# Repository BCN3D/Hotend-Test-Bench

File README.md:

# Hotend test bench
This project is a test bench for BCN3D Technologies.

It consist on a electronics Board to test out 6 Hotends at a time. It basically heats up the 6 hotends to a specified temperature and then cools them down.
It verifies that the time to do the cycle is correct.

![Hotend Test Jig][system]

[system]:  https://github.com/BCN3D/Hotend-Test-Jig/blob/master/img/system.JPG

#### Folders

- _BOM: _ here you can find the electronic components for the board.
- _Code:_ the files of the firmware for the microcontroller. It has been developed in Atmel Studio 7.0
- _Gerbers:_ the gerber files of the board.
- _TemperaturesPlotter:_ Processing file that plots the temperatures sent by the board. It is exported to Windows based systems in order to run the program without installing processing IDE.
- _Eagle files:_ original design files in CadSoft Eagle.
- _img:_ just some pictures of the project.

## Electronics
The electronics consist on a board with an ATmega328, 6 Power Mosfets and 2 Leds for each power channel to display the status.
The temperature is sensed by the hotend thermistors and each signal goes to a ADC channel of the microcontroller.

The 12 LEDs are driven by 2 8-bit shift registers.

It is powered by a 24V/320W switching Power supply and a +5V LDO for the logic.
For communication, it has FTDI compatible pin headers.

Board Front

![Board Front][board_front]

Board Rear

![Board Rear][board_rear]

[board_front]: https://github.com/BCN3D/Hotend-Test-Jig/blob/master/img/board_front.JPG
[board_rear]: https://github.com/BCN3D/Hotend-Test-Jig/blob/master/img/board_rear.JPG

## Code
The code uses the [PID library](http://playground.arduino.cc/Code/PIDLibrary) for Arduino and a home made [hotend class](https://github.com/BCN3D/Hotend-Test-Jig/blob/master/Code/hotend.h).

The conversion to temperature is calculated with the Steinhart-Hart equation. You can find the guidelines of this conversion in the [adafruit learning system](https://learn.adafruit.com/thermistor?view=all). It would be better to do some table look-up but the code is harder...

First it does a startup flashing the LEDs, opens a Serial port and then it checks if the hotends are connected or not by checking the thermistor resistance.

Then the heat up process starts. Every 500ms a packet is sent through the serial port with the six temperatures. This packet is received by the computer and a [Processing](http://processing.org) program plots the data.

Main Screen of the Processing program:

![TemperaturesPlotter][plotter]

[plotter]: https://github.com/BCN3D/Hotend-Test-Jig/blob/master/img/temperaturePlotter.PNG

When the  hotends are heating, the LEDs blink as well. Finally, when the target temperature is reached, the hotends start cooling down with the help of a couple of fans.

The code computes the time it took to heat up each hotend and then decides if the time is between the established limits.
## Mechanics

The Mechanics are quite simple. Basically we designed a bench to hold the hotends in place and to prevent the operator from burning. the black pieces are 3mm aluminum painted in matt black and the white pieces are 3D printed.

The cover from behind is a 3mm PMMA sheet laser cut and handcrafted bent.

## To do in the TemperaturesPlotter
- [ ] Clear button to clear the graph area.
- [ ] Start the time when the COM port is selected.
- [ ] Fix the target temperature bar to the correct temperature.
- [ ] Calculate the time to heat for each hotend
- [ ] Export data to a `.xmml` or `.csv` file and import it in Excel. To Database purposes
- [x] Splash Screen.
- [ ] Mouse gives you temperature in the graph.

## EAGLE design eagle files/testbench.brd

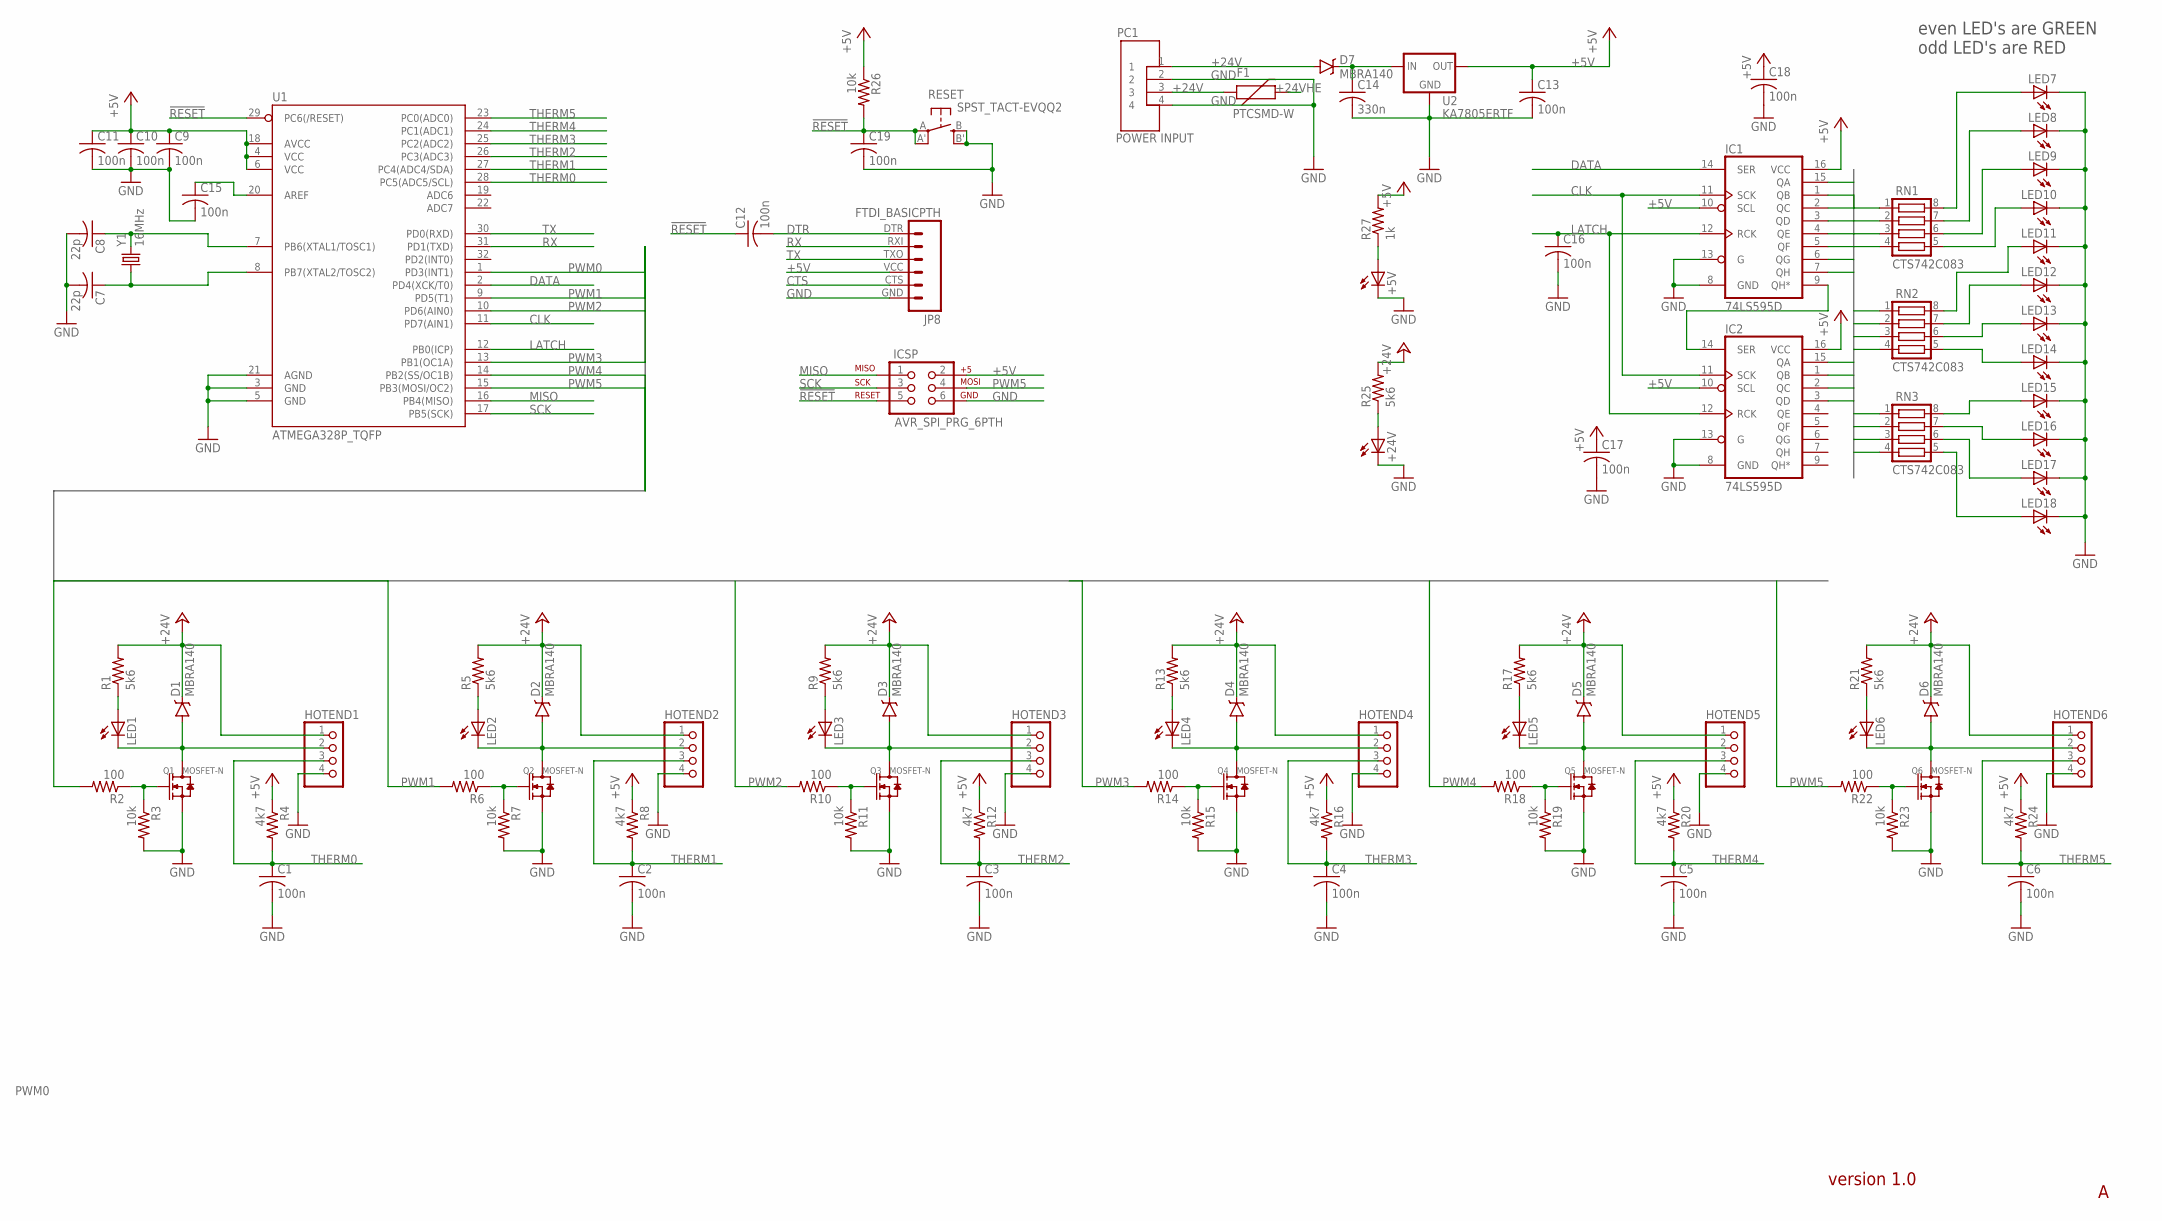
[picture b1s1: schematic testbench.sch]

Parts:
+5V, +24V: LEDCHIP-LED0805; CHIP-LED0805; MPN OVS-0803
C1, C2, C3, C4, C5, C6, C9, C10, C11, C12, C13, C15, C16, C17, C18, C19: 100n; C0805K; MPN 08051C104KAT2A
C7, C8: 22p; C0805K; MPN 08051A220JAT2A
C14: 330n; C0805K; MPN 08055C334KAT2A
D1, D2, D3, D4, D5, D6, D7: MBRA140; SMA-DIODE; MPN B140-13-F
F1: PTCSMD-W; PTC-1206-WIDE; MPN 3413.0329.22
HOTEND1, HOTEND2, HOTEND3, HOTEND4, HOTEND5, HOTEND6: PINHD-1X4; 1X04
IC1, IC2: 74LS595D; SO16; MPN SN74AHCT595D
ICSP: AVR_SPI_PRG_6PTH; 2X3
JP8: FTDI_BASICPTH; FTDI_BASIC
LED1, LED2, LED3, LED4, LED5, LED6, LED7, LED8, LED9, LED10, LED11, LED12, LED13, LED14, LED15, LED16, LED17, LED18: LEDCHIP-LED0805; CHIP-LED0805; MPN OVS-0803
PC1: POWER INPUT; MOLEX_MINIFIT-JR; MPN 39303045
Q1, Q2, Q3, Q4, Q5, Q6: MOSFET-N; SOIC8; MPN IRF8736PBF
R1, R5, R9, R13, R17, R21, R25: 5k6; R0805; MPN MCWR08X5601FTL
R2, R6, R10, R14, R18, R22: 100; R0805; MPN ERA6AEB101V
R3, R7, R11, R15, R19, R23, R26: 10k; R0805; MPN 0621-013K500-AB103
R4, R8, R12, R16, R20, R24: 4k7; R0805; MPN 1-2176085-7
R27: 1k; R0805; MPN CR0805-JW-102ELF
RESET: SPST_TACT-EVQQ2; EVQ-Q2; MPN EVQQ2503W
RN1, RN2, RN3: CTS742C083
U1: ATMEGA328P_TQFP; TQFP32-08; MPN ATMEGA328-AU
U2: KA7805ERTF; TO-252; MPN KA7805ERTF
Y1: 16MHz; HC49US; MPN 9B-20.000MAAJ-B

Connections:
!RESET: C12.1, C19.1, ICSP.5, R26.2, RESET.A, RESET.A' (P1), U1.29 (PC6(/RESET))
+5V: C9.1, C10.1, C11.1, C13.1, C17.1, C18.1, IC1.10 (SCL), IC1.16 (VCC), IC2.10 (SCL), IC2.16 (VCC), ICSP.2, JP8.VCC (4), R4.1, R8.1, R12.1, R16.1, R20.1, R24.1, R26.1, R27.2, U1.4 (VCC), U1.6 (VCC), U1.18 (AVCC), U2.2 (OUT)
+24V: D7.A, F1.1, PC1.1, PC1.3, R25.2
+24VHE: D1.C, D2.C, D3.C, D4.C, D5.C, D6.C, F1.2, HOTEND1.1, HOTEND2.1, HOTEND3.1, HOTEND4.1, HOTEND5.1, HOTEND6.1, R1.2, R5.2, R9.2, R13.2, R17.2, R21.2
CLK: IC1.11 (SCK), IC2.11 (SCK), U1.11 (PD7(AIN1))
CTS: JP8.CTS (5)
DATA: IC1.14 (SER), U1.2 (PD4(XCK/T0))
DTR: C12.2, JP8.DTR (1)
GND: +5V.C, +24V.C, C1.2, C2.2, C3.2, C4.2, C5.2, C6.2, C7.2, C8.2, C9.2, C10.2, C11.2, C13.2, C14.2, C15.2, C16.2, C17.2, C18.2, C19.2, HOTEND1.4, HOTEND2.4, HOTEND3.4, HOTEND4.4, HOTEND5.4, HOTEND6.4, IC1.8 (GND), IC1.13 (G), IC2.8 (GND), IC2.13 (G), ICSP.6, JP8.GND (6), LED7.C, LED8.C, LED9.C, LED10.C, LED11.C, LED12.C, LED13.C, LED14.C, LED15.C, LED16.C, LED17.C, LED18.C, PC1.2, PC1.4, Q1.1 (S), Q1.2 (S), Q1.3 (S), Q2.1 (S), Q2.2 (S), Q2.3 (S), Q3.1 (S), Q3.2 (S), Q3.3 (S), Q4.1 (S), Q4.2 (S), Q4.3 (S), Q5.1 (S), Q5.2 (S), Q5.3 (S), Q6.1 (S), Q6.2 (S), Q6.3 (S), R3.2, R7.2, R11.2, R15.2, R19.2, R23.2, RESET.B (S), RESET.B' (S1), U1.3 (GND), U1.5 (GND), U1.21 (AGND), U2.3 (GND)
H1: D1.A, HOTEND1.2, LED1.C, Q1.5 (D), Q1.6 (D), Q1.7 (D), Q1.8 (D)
H2: D2.A, HOTEND2.2, LED2.C, Q2.5 (D), Q2.6 (D), Q2.7 (D), Q2.8 (D)
H3: D3.A, HOTEND3.2, LED3.C, Q3.5 (D), Q3.6 (D), Q3.7 (D), Q3.8 (D)
H4: D4.A, HOTEND4.2, LED4.C, Q4.5 (D), Q4.6 (D), Q4.7 (D), Q4.8 (D)
H5: D5.A, HOTEND5.2, LED5.C, Q5.5 (D), Q5.6 (D), Q5.7 (D), Q5.8 (D)
H6: D6.A, HOTEND6.2, LED6.C, Q6.5 (D), Q6.6 (D), Q6.7 (D), Q6.8 (D)
LATCH: C16.1, IC1.12 (RCK), IC2.12 (RCK), U1.12 (PB0(ICP))
LED0: IC1.15 (QA), RN2.4
LED1: IC1.1 (QB), RN2.3
LED2: IC1.2 (QC), RN2.2
LED3: IC1.3 (QD), RN2.1
LED4: IC1.4 (QE), RN1.4
LED5: IC1.5 (QF), RN1.3
LED6: IC1.6 (QG), RN1.2
LED7: IC1.7 (QH), RN1.1
LED8: IC2.15 (QA), RN3.4
LED9: IC2.1 (QB), RN3.3
LED10: IC2.2 (QC), RN3.2
LED11: IC2.3 (QD), RN3.1
MISO: ICSP.1, U1.16 (PB4(MISO))
unnamed: Q1.4 (G), R2.1, R3.1
unnamed: +24V.A, R25.1
unnamed: LED1.A, R1.1
unnamed: Q5.4 (G), R18.1, R19.1
unnamed: C7.1, U1.8 (PB7(XTAL2/TOSC2)), Y1.1
unnamed: LED7.A, RN1.8
unnamed: Q2.4 (G), R6.1, R7.1
unnamed: LED2.A, R5.1
unnamed: Q3.4 (G), R10.1, R11.1
unnamed: LED3.A, R9.1
unnamed: Q4.4 (G), R14.1, R15.1
unnamed: LED4.A, R13.1
unnamed: LED5.A, R17.1
unnamed: Q6.4 (G), R22.1, R23.1
unnamed: LED6.A, R21.1
unnamed: C8.1, U1.7 (PB6(XTAL1/TOSC1)), Y1.2
unnamed: C15.1, U1.20 (AREF)
unnamed: C14.1, D7.C, U2.1 (IN)
unnamed: LED8.A, RN1.7
unnamed: LED9.A, RN1.6
unnamed: LED10.A, RN1.5
unnamed: LED11.A, RN2.8
unnamed: LED12.A, RN2.7
unnamed: LED13.A, RN2.6
unnamed: LED14.A, RN2.5
unnamed: LED15.A, RN3.8
unnamed: LED16.A, RN3.7
unnamed: LED17.A, RN3.6
unnamed: LED18.A, RN3.5
unnamed: IC1.9 (QH*), IC2.14 (SER)
unnamed: +5V.A, R27.1
PWM0: R2.2, U1.1 (PD3(INT1))
PWM1: R6.2, U1.9 (PD5(T1))
PWM2: R10.2, U1.10 (PD6(AIN0))
PWM3: R14.2, U1.13 (PB1(OC1A))
PWM4: R18.2, U1.14 (PB2(SS/OC1B))
PWM5: ICSP.4, R22.2, U1.15 (PB3(MOSI/OC2))
RX: JP8.RXI (2), U1.31 (PD1(TXD))
SCK: ICSP.3, U1.17 (PB5(SCK))
THERM0: C1.1, HOTEND1.3, R4.2, U1.28 (PC5(ADC5/SCL))
THERM1: C2.1, HOTEND2.3, R8.2, U1.27 (PC4(ADC4/SDA))
THERM2: C3.1, HOTEND3.3, R12.2, U1.26 (PC3(ADC3))
THERM3: C4.1, HOTEND4.3, R16.2, U1.25 (PC2(ADC2))
THERM4: C5.1, HOTEND5.3, R20.2, U1.24 (PC1(ADC1))
THERM5: C6.1, HOTEND6.3, R24.2, U1.23 (PC0(ADC0))
TX: JP8.TXO (3), U1.30 (PD0(RXD))

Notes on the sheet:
even LED's are GREEN odd LED's are RED
version 1.0

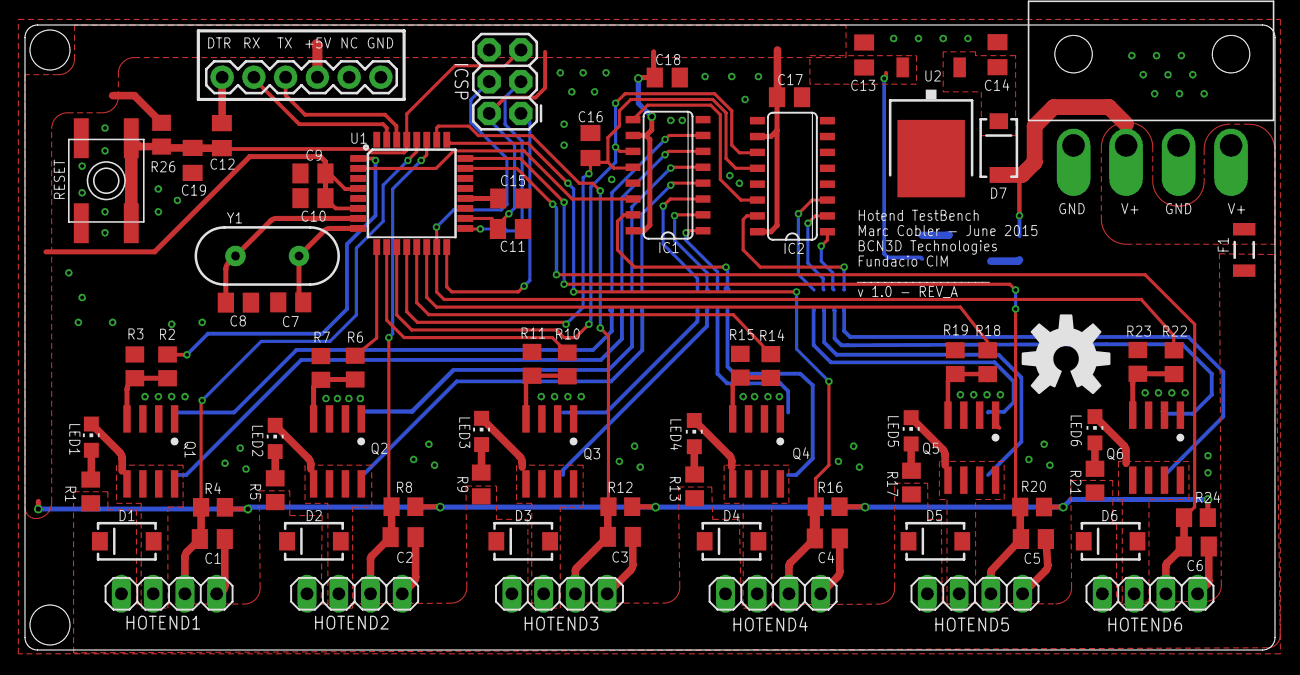
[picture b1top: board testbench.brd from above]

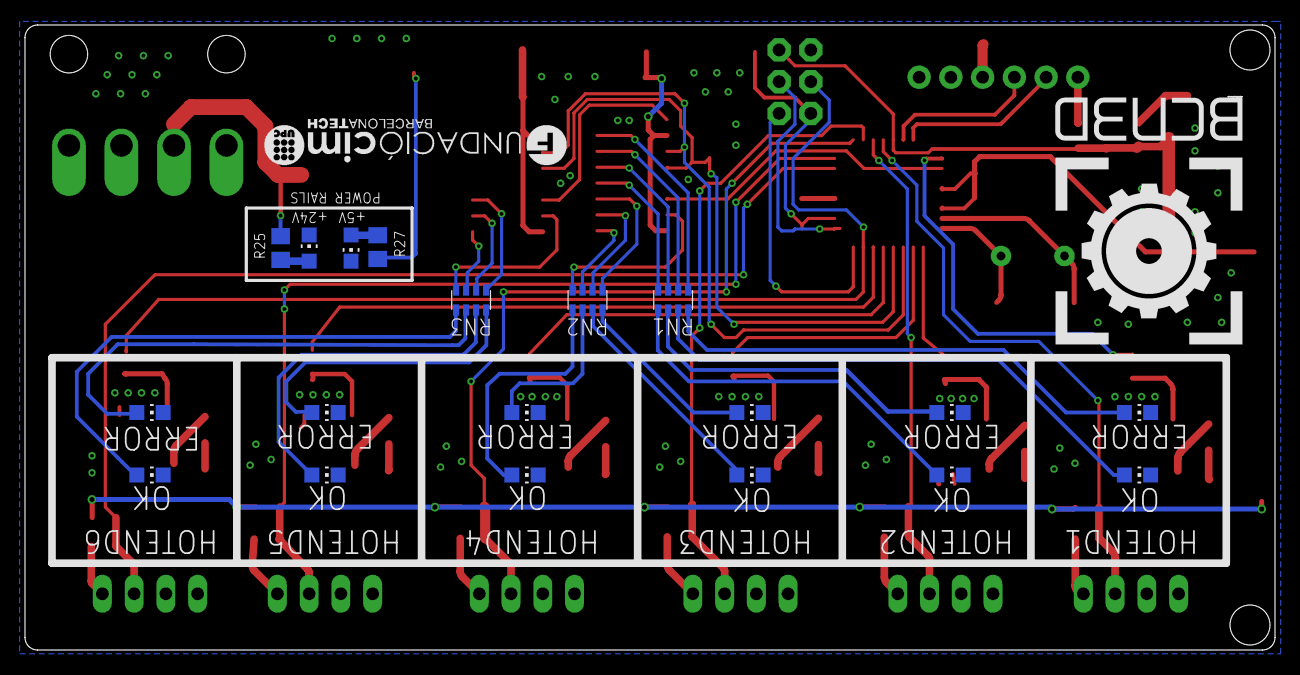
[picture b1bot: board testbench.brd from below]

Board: 2 copper layers, 100.0 x 50.0 mm, 101 parts (21 on the bottom side), 74 nets.

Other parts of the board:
U$1: FCIM_LOGO
U$2: BCN3D_LOGO
U$3: OSHW-LOGO-L

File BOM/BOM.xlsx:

Qty | Value | Device | Package | Parts | Description | MF | MPN | OC_FARNELL | OC_NEWARK | PROD_ID | VALUE
20 |  | LEDCHIP-LED0805 | CHIP-LED0805 | +5V, +24V, LED1, LED2, LED3, LED4, LED5, LED6, LED7, LED8, LED9, LED10, LED11, 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 | LED | MULTICOMP | OVS-0803 | 1716765
6 |  | PINHD-1X4 | 1X04 | HOTEND1, HOTEND2, HOTEND3, HOTEND4, HOTEND5, HOTEND6 | PIN HEADER |  |  | unknown
6 | 100 | R-US_R0805 | R0805 | R2, R6, R10, R14, R18, R22 | RESISTOR, American symbol | PANASONIC ELECTRONIC COMPONENTS | ERA6AEB101V | 1577644
16 | 100n | C-USC0805K | C0805K | C1, C2, C3, C4, C5, C6, C9, C10, C11, C12, C13, C15, C16, C17, C18, C19 | CAPACITOR, American symbol | AVX | 08051C104KAT2A | 1740681
7 | 10k | R-US_R0805 | R0805 | R3, R7, R11, R15, R19, R23, R26 | RESISTOR, American symbol | BOURNS | 0621-013K500-AB103 | 2469474
1 | 1k | R-US_R0805 | R0805 | R27 | RESISTOR, American symbol | BOURNS | CR0805-JW-102ELF | 2008389
1 | 20MHz | CRYSTALHC49US | HC49US | Y1 | Various standard crystals. Proven footprints. | TXC | 9B-20.000MAAJ-B | 1842224
2 | 22p | C-USC0805K | C0805K | C7, C8 | CAPACITOR, American symbol | AVX | 08051A220JAT2A | 317500
1 | 330n | C-USC0805K | C0805K | C14 | CAPACITOR, American symbol | AVX | 08055C334KAT2A | 1657934
6 | 4k7 | R-US_R0805 | R0805 | R4, R8, R12, R16, R20, R24 | RESISTOR, American symbol | TE CONNECTIVITY | 1-2176085-7 | 2118118
7 | 5k6 | R-US_R0805 | R0805 | R1, R5, R9, R13, R17, R21, R25 | RESISTOR, American symbol | MULTICOMP | MCWR08X5601FTL | 2447693
2 | 74LS595D | 74LS595D | SO16 | IC1, IC2 | 8-bit SHIFT REGISTER, output latch | TEXAS INSTRUMENTS | SN74HC165DR | 2436975 |  | IC-07875
1 | ATMEGA328P_TQFP | ATMEGA328P_TQFP | TQFP32-08 | U1 |  | ATMEL | ATMEGA328-AU | 1972086 |  | IC-09069 | ATMEGA328P_TQFP
1 | AVR_SPI_PRG_6PTH | AVR_SPI_PRG_6PTH | 2X3 | ICSP | AVR ISP 6 Pin |  |  | unknown
3 | CTS742C083 | CTS742C083 | CTS742C083 | RN1, RN2, RN3 | Chip Resistor Array 4 Single Resistor |  |  | unknown | unknown
1 | FTDI_BASICPTH | FTDI_BASICPTH | FTDI_BASIC | JP8 | FTDI Basic header with labels |  |  | unknown
1 | KA7805ERTF | V_REG_78XX7812 | TO-252 | U2 | Voltage Regulator | FAIRCHILD SEMICONDUCTOR | KA7805ERTF | 2102585 |  | VREG-12370 | +12v
7 | MBRA140 | MBRA140 | SMA-DIODE | D1, D2, D3, D4, D5, D6, D7 | 40V, 1A Schottky rectifier | DIODES INC. | B140-13-F | 1843670 |  | DIO-08053
6 | MOSFET-N | MOSFET-N | SOIC8 | Q1, Q2, Q3, Q4, Q5, Q6 | CJ2302:SMD MOSFET N-CH 20V-2.1A | INTERNATIONAL RECTIFIER | IRF8736PBF | 1551903
1 | POWER INPUT | POWER_CONNECTOR_4WAY | MOLEX_MINIFIT-JR | PC1 | MOLEX Mini-Fit Jr. 13A/600V Power connector REF: 39303045 | MOLEX | 39303045 | 9963553
1 | PTCSMD-W | PTCSMD-W | PTC-1206-WIDE | F1 | Resettable Fuse PTC | SCHURTER | 3413.0329.22 | 1829472
1 | SPST_TACT-EVQQ2 | SPST_TACT-EVQQ2 | EVQ-Q2 | RESET | SMT 6mm switch, EVQQ2 series | PANASONIC ELECTRONIC COMPONENTS | EVQQ2503W | 9962913

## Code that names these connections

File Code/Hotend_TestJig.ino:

/*---------------------------------------------------------------------
Hotend_TestJig.ino - main program file
HotEnd test Jig
Marc Cobler Cosmen - June 2015
BCN3D Technologies - Fundacio CIM

This program is for testing the assembled hotends in BCN3D Technologies.
It's Atmega328 based and it contains 6 power Mosfet Channels to heat up
6 hotends at a time. If the heating curve is within limits, then a Green 
LED lights up, if not a red LED lights up.


ADJUSTING PWM FREQUENCIES 
In the Arduino world timer0 is been used for the timer functions, like delay(), millis() and micros(). 
If you change timer0 registers, this may influence the Arduino timer function. 
So you should know what you are doing. 
// Note that the base frequency for pins 3, 9, 10, and 11 is 31250 Hz
// Note that the base frequency for pins 5 and 6 is 62500 Hz
-----------------------------------------------------------------------*/
#include "hotend.h"
#include "PID_v1.h"
//--------------------CONSTANTS-----------------------------------------
#define MAXTEMPERATURE 260

const char* tempSensors[]= {"THERM0","THERM1","THERM2","THERM3","THERM4","THERM5"};
#define THERM0 5
#define THERM1 4
#define THERM2 3
#define THERM3 2
#define THERM4 1
#define THERM5 0

#define HOTEND0 3 //PD3 TIMER2
#define HOTEND1 5 //PD5 TIMER0
#define HOTEND2 6 //PD6 TIMER0
#define HOTEND3 9 //PB1 TIMER1
#define HOTEND4 10 //PB2 TIMER1
#define HOTEND5 11 //PB3 TIMER2

#define CLOCK 7
#define LATCH 8
#define DATA 4

//--------------------VARIABLES-----------------------------------------
bool connectedHotends[6]= {0,0,0,0,0,0}; //Array of boolean. Indicates hotends connected
String command;
//PID Variables
double output;
double setTemperature;
//PID Settings
double kp = 1;
double kd = 0.25;
double ki = 0.05;
//bytes for the shift Registers
byte leds1 = 0;
byte leds2 = 0;


//--------------------OBJECTS-------------------------------------------
//---Let's declare de hotends objects
hotend h1(THERM0, HOTEND0);
hotend h2(THERM1, HOTEND1);
hotend h3(THERM2, HOTEND2);
hotend h4(THERM3, HOTEND3);
hotend h5(THERM4, HOTEND4);
hotend h6(THERM5, HOTEND5);

PID hotendPID1(&h1.tempCelsius, &output, &setTemperature, kp, ki, kd, DIRECT);
PID hotendPID2(&h2.tempCelsius, &output, &setTemperature, kp, ki, kd, DIRECT);
PID hotendPID3(&h3.tempCelsius, &output, &setTemperature, kp, ki, kd, DIRECT);
PID hotendPID4(&h4.tempCelsius, &output, &setTemperature, kp, ki, kd, DIRECT);
PID hotendPID5(&h5.tempCelsius, &output, &setTemperature, kp, ki, kd, DIRECT);
PID hotendPID6(&h6.tempCelsius, &output, &setTemperature, kp, ki, kd, DIRECT);

hotend hotends[] = {h1,h2,h3,h4,h5,h6};
PID PIDS[] = {hotendPID1, hotendPID2, hotendPID3, hotendPID4, hotendPID5, hotendPID6};

void setup()
{
  pinMode(CLOCK, OUTPUT);
  pinMode(LATCH, OUTPUT);
  pinMode(DATA, OUTPUT);
  digitalWrite(CLOCK, LOW);
  //No need to declare analog pins as inputs
  //Set the PWM frequency to 3906.25Hz on Timer 1 and 2
  setPwmFrequency(HOTEND0, 8); //Pins 3 and 11 are paired on timer 2 so only need to change one
  setPwmFrequency(HOTEND3, 8); //Pins 9 and 10 are paired on timer 1 so only need to change one
  
  setTemperature = MAXTEMPERATURE;
  hotendPID1.SetMode(AUTOMATIC);
  hotendPID2.SetMode(AUTOMATIC);
  hotendPID3.SetMode(AUTOMATIC);
  hotendPID4.SetMode(AUTOMATIC);
  hotendPID5.SetMode(AUTOMATIC);
  hotendPID6.SetMode(AUTOMATIC);
  
  Serial.begin(115200);
  Serial.println("Starting the Hotend Test Jig...");
  delay(2000);
  Serial.println("Checking connected hotends");
  checkConnectedHotends();
}
void loop()
{
	uint8_t i;
	commands();
	for (i = 0; i < 6; i++)
	{
		if (connectedHotends[i] == 1)	
		{
			hotends[i].readTemperature();
			PIDS[i].Compute();
			hotends[i].update(output, i);
			if (hotends[i].state == 1)
			{
				manageLEDs(hotends[i].hotendState, i);
			}
		}
	}
}
//--------------------USER FUNCTIONS----------------------
void setPwmFrequency(int pin, int divisor) {
	byte mode;
	if(pin == 5 || pin == 6 || pin == 9 || pin == 10) {
		switch(divisor) {
			case 1: mode = 0x01; break;
			case 8: mode = 0x02; break;
			case 64: mode = 0x03; break;
			case 256: mode = 0x04; break;
			case 1024: mode = 0x05; break;
			default: return;
		}
		if(pin == 5 || pin == 6) {
			TCCR0B = TCCR0B & 0b11111000 | mode;
			} else {
			TCCR1B = TCCR1B & 0b11111000 | mode;
		}
		} else if(pin == 3 || pin == 11) {
		switch(divisor) {
			case 1: mode = 0x01; break;
			case 8: mode = 0x02; break;
			case 32: mode = 0x03; break;
			case 64: mode = 0x04; break;
			case 128: mode = 0x05; break;
			case 256: mode = 0x06; break;
			case 1024: mode = 0x7; break;
			default: return;
		}
		TCCR2B = TCCR2B & 0b11111000 | mode;
	}
}
void checkConnectedHotends() {
	uint8_t i;
	for (i = 0; i<= 5; i++)
	{
		hotends[i].readTemperature();
		if (hotends[i].averageTemp >= 1000) 
		{
			//Hotend i not connected
			connectedHotends[i] = 0;
			Serial.print("Hotend ");
			Serial.print(i + 1, DEC);
			Serial.println(" not present");
		} else { 
			//Hotend i present and with a valid reading
			connectedHotends[i] = 1;
			Serial.print("Hotend ");
			Serial.print(i + 1, DEC);
			Serial.println(" connected!");
		}
	}
}
void manageLEDs(bool status, uint8_t pos) {
	//Manage the leds throught the Shift Registers
	if (status)
	{
		//Green LED must be turned on
		if (pos < 4)
		{
			bitSet(leds1, 2*pos + 1);
		} else {
			bitSet(leds2, 2*pos - 3);
		}
	} else {
		//Red LED must be turned on
		if (pos < 4)
		{
			bitSet(leds1, 2*pos );
		} else {
			bitSet(leds2, 2*pos - 4);
		}
	}
	digitalWrite(LATCH, LOW);
	shiftOut(DATA, CLOCK, LSBFIRST, leds2);
	shiftOut(DATA, CLOCK, LSBFIRST, leds1);
	digitalWrite(LATCH, HIGH);
}
void setPIDtunings(double Kp, double Ki, double Kd) {
	kp = Kp;
	ki = Ki;
	kd = Kd;
}
void commands()	{
	while (Serial.available() > 0)
	{
		char c = Serial.read();
		if (c == '\n')
		{
			parseCommand(command);
			command = "";
		}
		else
		{
			command += c;
		}
	}
}
void parseCommand(String com)	{
	//the commands will ignore the Case, so it could be:
	double kpTemp = 0;
	double kiTemp = 0;
	double kdTemp = 0;
	
	String part1, part2;
	bool twoArgCommand;
	int s = 0;
	while (com[s] != ' ' && s <= (com.length()-1)){
		//If found a blank space and s is less than com length-->out
		s++;
	}
	if (s < com.length())
	{
		Serial.println("Found a space in the command");
		twoArgCommand = true;
		part1 = com.substring(0, com.indexOf(" "));
		part2 = com.substring(com.indexOf(" ") + 1, com.length());
	} else if(s == com.length())
	{
		Serial.println("No space in the command");
		twoArgCommand = false;
		part1 = com.substring(0, com.length()-1);
		part2 = "";
	}
	
	Serial.print("the command is: ");
	Serial.print(part1);
	Serial.print(" ");
	Serial.println(part2);
	
	if (part1.equalsIgnoreCase("kp"))
	{
		kpTemp = part2.toFloat();
	} else if (part1.equalsIgnoreCase("kd"))
	{
		kdTemp = part2.toFloat();
	} else if (part1.equalsIgnoreCase("ki"))
	{
		kiTemp = part2.toFloat();
	} else if (part1.equalsIgnoreCase("showinfo"))
	{
		//Prints out the PID settings like de kp ki kd and Mode
		Serial.print("Kp: ");
		Serial.println(hotendPID1.GetKp());
		Serial.print("Ki: ");
		Serial.println(hotendPID1.GetKi());
		Serial.print("Kd: ");
		Serial.println(hotendPID1.GetKd());
		Serial.print("Mode: ");
		Serial.println(hotendPID1.GetMode());
		Serial.println("Direction: ");
		Serial.println(hotendPID1.GetDirection());
	}
	
	
	if (kpTemp != 0 && kdTemp != 0 && kiTemp != 0)
	{
		setPIDtunings(kpTemp, kiTemp, kdTemp);
		kpTemp = 0;
		kiTemp = 0;
		kdTemp = 0;
	}
		
	
}

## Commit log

2015-06-16 :confetti_ball: Added .gitattributes
2015-06-16 Version 0.9 of the Board
    First stable version of the Extruder test jig. Waiting for the PCB's to
    be manufactured
2015-06-22 v 1.0 - REV_A
    You can find all the gerbers and the BOM. Sent to Fab House.
2015-07-14 All the code for the Hotend Test Jig!
    Updated BOM
    All the code, untested yet
    Updated crystal frequency
2015-11-13 changes in file tree and updates
    Now we have a tested stable version. The PID values are not tuned yet.
2015-11-13 update file tree and Processing
    New Processing sketch that plots the temperature of the hotends to fine
    tune the PID and to check for differences.
2015-11-13 Added axis marks in the graph
2015-11-17 Some tweaking and better processing
2015-11-17 securityBlink()
    this functions tells you through the leds if you can hold the hotend
    depending on the temperature
2015-11-18 Exporting to windows application
2015-11-18 New COM Port Selection screen
    Before the graph it lets you select the correct COM Port and connect to
    the board
2015-11-20 Splash screen implementation
    Splash screen with a rotating BCN3D Logo!
2015-11-23 Splash screen now working
    Added descriptions of functions and some bug fixes
2015-11-23 Updated version of the windows app
2015-11-24 Change the PID Values and the target temperature.
2015-11-24 Some images and updated README
2015-11-24 img to the README
2015-11-24 map() function to draw the target temp line
2016-11-02 added photo
2016-11-04 Print Settings @ startup and some corrections
2017-04-20 Update with Atmel Studio Project files
2017-05-18 Minor corrections and updates!

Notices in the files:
parts and their libraries:
SparkFun-DiscreteSemi: Licensing: Creative Commons ShareAlike 4.0 International - https://creativecommons.org/licenses/by-sa/4.0
